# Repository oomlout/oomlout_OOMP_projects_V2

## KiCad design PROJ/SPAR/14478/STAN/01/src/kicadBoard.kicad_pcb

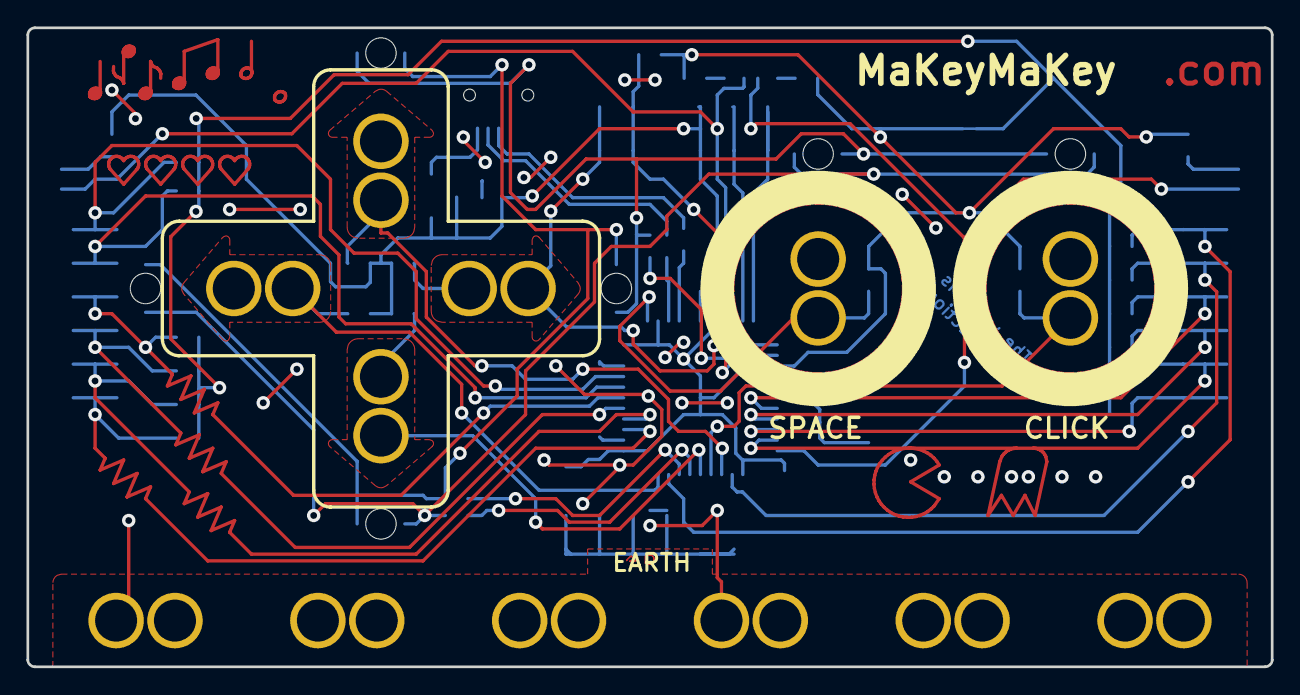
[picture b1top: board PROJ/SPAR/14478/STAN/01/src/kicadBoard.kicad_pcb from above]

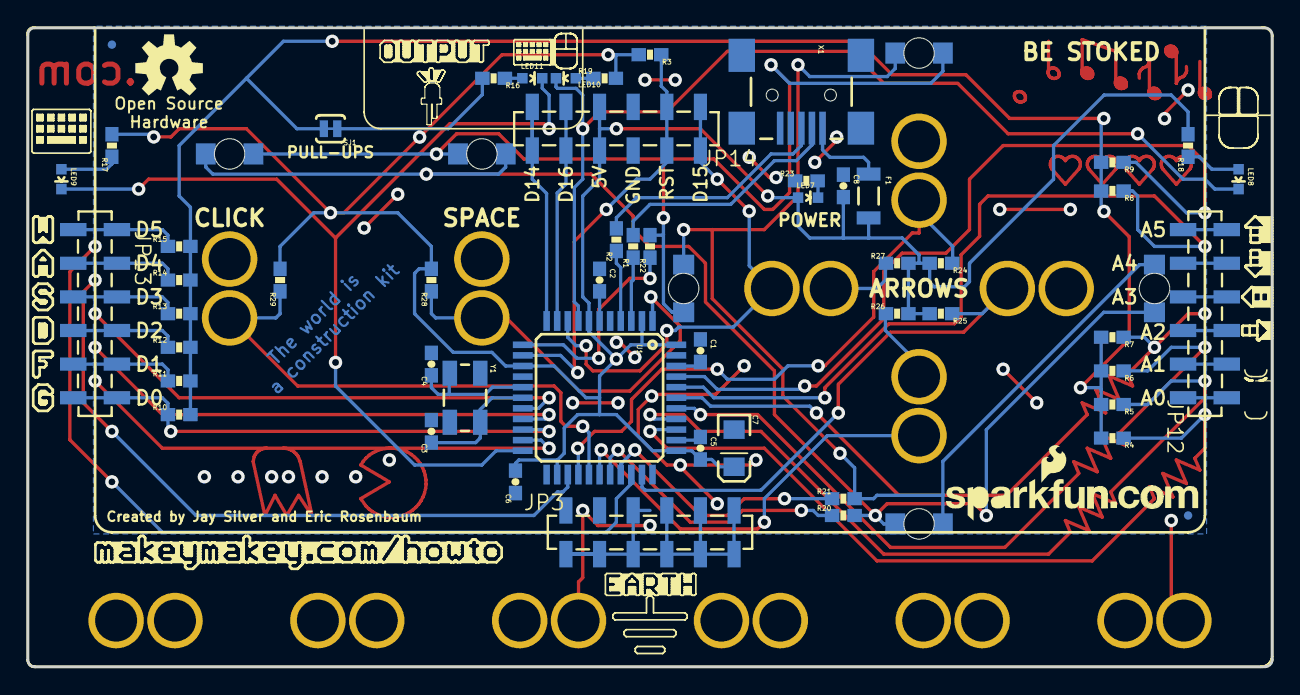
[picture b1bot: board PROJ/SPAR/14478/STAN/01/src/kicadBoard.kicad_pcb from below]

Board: 2 copper layers, 94.0 x 48.3 mm, 73 parts (63 on the bottom side), 46 nets.

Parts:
C1, C5, C8: 0.1uF; 0603-CAP
C2, C6: 1uF; 0603-CAP
C3, C4: 22pF; 0603-CAP
C7: 10uF; EIA3216
CLICK0: 1X01_ALLIGATOR_3MM
DOWN0: 1X01_ALLIGATOR_3MM
F1: 500mA; PTC-1206-WIDE
JP1, JP2: FIDUCIALUFIDUCIAL; MICRO-FIDUCIAL
JP3, JP12, JP13, JP14: 1X06_SMD_STRAIGHT_COMBO
JP5, JP6, JP7, JP8, JP10, JP11: 1X01_ALLIGATOR_3MM
JP9: LOGO-SFENEW; SFE-NEW-WEBLOGO
LED1, LED2, LED3, LED4, LED5, LED6: GREEN; LED-1206-BOTTOM
LED7, LED10, LED11: RED; LED-0603
LED8, LED9: GREEN; LED-0603
LEFT0: 1X01_ALLIGATOR_3MM
R1, R2: 22; 0603-RES
R3: 10K; 0603-RES
R4, R5, R6, R7, R8, R9, R10, R11, R12, R13, R14, R15, R24, R25, R26, R27, R28, R29: 22M; 0603-RES
R16, R19, R23: 1k; 0603-RES
R17, R18, R20, R21, R22: 330; 0603-RES
RIGHT0: 1X01_ALLIGATOR_3MM
SJ1: Pull-ups; SJ_2S-TRACE
SPACE0: 1X01_ALLIGATOR_3MM
U1: ATMEGA32U4TQFP; TQFP44
U$1: OSHW-LOGOM; OSHW-LOGO-M
UP0: 1X01_ALLIGATOR_3MM
X1: USBSMD; USB-MINIB
Y1: 16MHz; CRYSTAL-SMD-5X3

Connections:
A0: JP12.1, JP12.1-2, R4.1, U1.36
A1: JP12.2, JP12.2-2, R5.1, U1.37
A2: JP12.3, JP12.3-2, R6.1, U1.38
A3: JP12.4, JP12.4-2, R7.1, U1.39
A4: JP12.5, JP12.5-2, R8.1, U1.40
A5: JP12.6, JP12.6-2, R9.1, U1.41
AREF: C1.2, U1.42
D0: JP13.6, JP13.6-2, R10.1, U1.20
D1: JP13.5, JP13.5-2, R11.1, U1.21
D2: JP13.4, JP13.4-2, R12.1, U1.19
D3: JP13.3, JP13.3-2, R13.1, U1.18
D4: JP13.2, JP13.2-2, R14.1, U1.25
D5: JP13.1, JP13.1-2, R15.1, U1.31
D6: CLICK0.1@0, CLICK0.1@2, R29.1, U1.27
D7: R28.1, SPACE0.1@0, SPACE0.1@2, U1.1
D8: DOWN0.1@0, DOWN0.1@2, R26.1, U1.28
D9: R20.1, U1.29
D10: R21.1, U1.30
D11: R22.1, U1.12
D12: R24.1, U1.26, UP0.1@0, UP0.1@2
D13: LEFT0.1@0, LEFT0.1@2, R25.1, U1.32
D14: JP14.6, JP14.6-2, U1.11
D15: JP14.1, JP14.1-2, R27.1, RIGHT0.1@0, RIGHT0.1@2, U1.9
D16: JP14.5, JP14.5-2, U1.10
D17: LED8.C, LED10.C, U1.8
D+: R2.1, U1.4
D-: R1.1, U1.3
GND: C1.1, C2.1, C3.2, C4.2, C5.1, C6.1, C7.C, C8.1, JP3.1, JP3.1-2, JP3.2, JP3.2-2, JP3.3, JP3.3-2, JP3.4, JP3.4-2, JP3.5, JP3.5-2, JP3.6, JP3.6-2, JP5.1@0, JP5.1@2, JP6.1@0, JP6.1@2, JP7.1@0, JP7.1@2, JP8.1@0, JP8.1@2, JP10.1@0, JP10.1@2, JP11.1@0, JP11.1@2, JP14.3, JP14.3-2, R23.1, U1.5, U1.15, U1.23, U1.33, U1.35, U1.43, X1.GND
unnamed: C4.1, U1.16, Y1.1
unnamed: C3.1, U1.17, Y1.3
unnamed: LED8.A, R18.1
unnamed: C2.2, U1.6
unnamed: F1.1, X1.VBUS
unnamed: R1.2, X1.D-
unnamed: LED7.C, R23.2
unnamed: R2.2, X1.D+
unnamed: LED11.A, R16.1
unnamed: LED10.A, R19.1
unnamed: LED9.A, R17.1
unnamed: LED1.C, LED2.A, LED5.A, LED6.C, R21.2
unnamed: LED1.A, LED2.C, LED3.A, LED4.C, R20.2
unnamed: LED3.C, LED4.A, LED5.C, LED6.A, R22.2
PD5: LED9.C, LED11.C, U1.22
PULL-UP: R4.2, R5.2, R6.2, R7.2, R8.2, R9.2, R10.2, R11.2, R12.2, R13.2, R14.2, R15.2, SJ1.2
RESET: JP14.2, JP14.2-2, R3.1, U1.13
VCC: C5.2, C6.2, C7.A, C8.2, F1.2, JP14.4, JP14.4-2, LED7.A, R3.2, R16.2, R17.2, R18.2, R19.2, R24.2, R25.2, R26.2, R27.2, R28.2, R29.2, SJ1.1, U1.2, U1.7, U1.14, U1.24, U1.34, U1.44

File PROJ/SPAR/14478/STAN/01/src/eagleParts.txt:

Partlist

Exported from boardEagle.brd at 20/08/2022 00:19

EAGLE Version 9.6.2 Copyright (c) 1988-2020 Autodesk, Inc.

Assembly variant: 

Part     Value             Package                 Library             Position (inch)       Orientation

C1       0.1uF             0603-CAP                SparkFun            (1.7 0.94)            MR270
C2       1uF               0603-CAP                SparkFun            (2 1.15)              MR270
C3       22pF              0603-CAP                SparkFun            (2.5 0.7)             MR90
C4       22pF              0603-CAP                SparkFun            (2.5 0.9)             MR90
C5       0.1uF             0603-CAP                SparkFun            (1.7 0.65)            MR270
C6       1uF               0603-CAP                SparkFun            (2.25 0.55)           MR90
C7       10uF              EIA3216                 SparkFun            (1.6 0.65)            MR270
C8       0.1uF             0603-CAP                SparkFun            (1.275 1.43)          MR270
CLICK                      1X01_ALLIGATOR_3MM      SparkFun-Connectors (3.1 1.125)           MR180
DOWN                       1X01_ALLIGATOR_3MM      SparkFun-Connectors (1.05 0.775)          R0
F1       500mA             PTC-1206-WIDE           SparkFun-PowerIC    (1.2 1.4)             MR270
JP1      FIDUCIALUFIDUCIAL MICRO-FIDUCIAL          SparkFun            (3.45 1.85)           MR0
JP2      FIDUCIALUFIDUCIAL MICRO-FIDUCIAL          SparkFun            (0.25 0.45)           MR0
JP3                        1X06_SMD_STRAIGHT_COMBO SparkFun-Connectors (2.1 0.4)             MR0
JP5                        1X01_ALLIGATOR_3MM      SparkFun-Connectors (3.35 0.1375)         R90
JP6                        1X01_ALLIGATOR_3MM      SparkFun-Connectors (2.75 0.1375)         R90
JP7                        1X01_ALLIGATOR_3MM      SparkFun-Connectors (2.15 0.1375)         R90
JP8                        1X01_ALLIGATOR_3MM      SparkFun-Connectors (1.55 0.1375)         R90
JP10                       1X01_ALLIGATOR_3MM      SparkFun-Connectors (0.95 0.1375)         R90
JP11                       1X01_ALLIGATOR_3MM      SparkFun-Connectors (0.35 0.1375)         R90
JP12                       1X06_SMD_STRAIGHT_COMBO SparkFun-Connectors (0.2 0.8)             MR90
JP13                       1X06_SMD_STRAIGHT_COMBO SparkFun-Connectors (3.5 1.3)             MR270
JP14                       1X06_SMD_STRAIGHT_COMBO SparkFun-Connectors (1.7 1.6)             MR180
LED1     GREEN             LED-1206-BOTTOM         SparkFun-LED        (1.05 0.425)          MR0
LED2     GREEN             LED-1206-BOTTOM         SparkFun-LED        (0.35 1.125)          MR270
LED3     GREEN             LED-1206-BOTTOM         SparkFun-LED        (3.1 1.525)           MR0
LED4     GREEN             LED-1206-BOTTOM         SparkFun-LED        (2.35 1.525)          MR0
LED5     GREEN             LED-1206-BOTTOM         SparkFun-LED        (1.05 1.825)          MR0
LED6     GREEN             LED-1206-BOTTOM         SparkFun-LED        (1.75 1.125)          MR90
LED7     RED               LED-0603                SparkFun            (1.38 1.395)          MR270
LED8     GREEN             LED-0603                SparkFun-LED        (0.1 1.45)            MR180
LED9     GREEN             LED-0603                SparkFun-LED        (3.6 1.45)            MR180
LED10    RED               LED-0603                SparkFun-LED        (2.1 1.75)            MR90
LED11    RED               LED-0603                SparkFun-LED        (2.2 1.75)            MR270
LEFT                       1X01_ALLIGATOR_3MM      SparkFun-Connectors (0.7 1.125)           R270
R1       22                0603-RES                SparkFun            (1.9 1.25)            MR90
R2       22                0603-RES                SparkFun            (1.95 1.27)           MR90
R3       10K               0603-RES                SparkFun            (1.85 1.82)           MR180
R4       22M               0603-RES                SparkFun            (0.475 0.68)          MR180
R5       22M               0603-RES                SparkFun            (0.475 0.78)          MR180
R6       22M               0603-RES                SparkFun            (0.475 0.88)          MR180
R7       22M               0603-RES                SparkFun            (0.475 0.98)          MR180
R8       22M               0603-RES                SparkFun            (0.475 1.415)         MR180
R9       22M               0603-RES                SparkFun            (0.475 1.5)           MR180
R10      22M               0603-RES                SparkFun            (3.25 0.75)           MR0
R11      22M               0603-RES                SparkFun            (3.25 0.85)           MR0
R12      22M               0603-RES                SparkFun            (3.25 0.95)           MR0
R13      22M               0603-RES                SparkFun            (3.25 1.05)           MR0
R14      22M               0603-RES                SparkFun            (3.25 1.15)           MR0
R15      22M               0603-RES                SparkFun            (3.25 1.25)           MR0
R16      1k                0603-RES                SparkFun-Passives   (2.315 1.75)          MR180
R17      330               0603-RES                SparkFun-Passives   (3.45 1.55)           MR90
R18      330               0603-RES                SparkFun-Passives   (0.25 1.55)           MR90
R19      1k                0603-RES                SparkFun-Passives   (1.985 1.75)          MR0
R20      330               0603-RES                SparkFun-Passives   (1.275 0.45)          MR0
R21      330               0603-RES                SparkFun-Passives   (1.275 0.5)           MR0
R22      330               0603-RES                SparkFun-Passives   (1.85 1.25)           MR90
R23      1k                0603-RES                SparkFun            (1.385 1.445)         MR0
R24      22M               0603-RES                SparkFun            (0.985 1.2)           MR180
R25      22M               0603-RES                SparkFun            (0.985 1.05)          MR180
R26      22M               0603-RES                SparkFun            (1.115 1.05)          MR0
R27      22M               0603-RES                SparkFun            (1.115 1.2)           MR0
R28      22M               0603-RES                SparkFun            (2.5 1.15)            MR90
R29      22M               0603-RES                SparkFun            (2.95 1.15)           MR90
RIGHT                      1X01_ALLIGATOR_3MM      SparkFun-Connectors (1.4 1.125)           R270
SJ1      Pull-ups          SJ_2S-TRACE             SparkFun            (2.8 1.6)             MR180
SPACE                      1X01_ALLIGATOR_3MM      SparkFun-Connectors (2.35 1.125)          MR180
U1       ATMEGA32U4TQFP    TQFP44                  SparkFun-DigitalIC  (2 0.8)               MR270
UP                         1X01_ALLIGATOR_3MM      SparkFun-Connectors (1.05 1.475)          R0
X1       USBSMD            USB-MINIB               SparkFun            (1.4 1.7)             MR270
Y1       16MHz             CRYSTAL-SMD-5X3         SparkFun            (2.4 0.8)             MR270

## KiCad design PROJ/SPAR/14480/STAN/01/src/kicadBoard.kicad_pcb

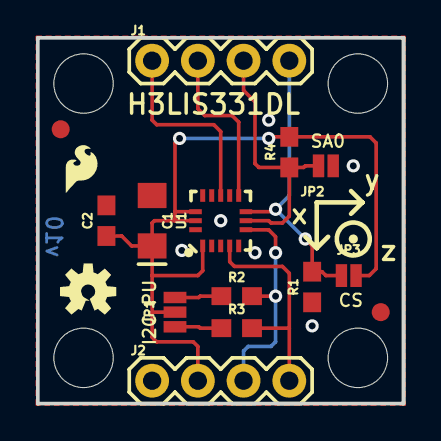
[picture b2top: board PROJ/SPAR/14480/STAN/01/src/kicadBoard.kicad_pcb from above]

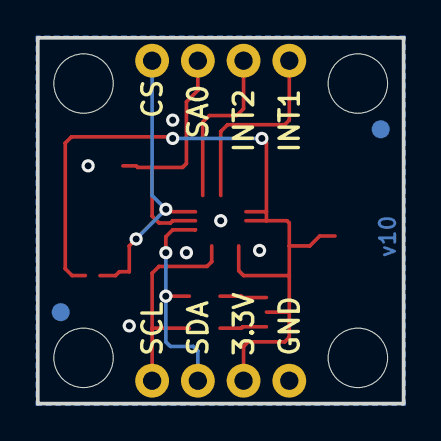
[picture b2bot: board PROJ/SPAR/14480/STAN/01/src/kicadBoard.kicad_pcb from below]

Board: 4 copper layers, 20.3 x 20.3 mm, 23 parts (2 on the bottom side), 10 nets.

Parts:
C1: 10uF; EIA3216
C2: 0.1uF; 0603
FRAME1: FRAME-LETTER; CREATIVE_COMMONS
J1, J2: 1X04
JP1: JUMPER-SMT_3_2-NC_PASTE_NO-SILK; SMT-JUMPER_3_2-NC_PASTE_NO-SILK
JP2: JUMPER-SMT_2_NO_NO-SILK; SMT-JUMPER_2_NO_NO-SILK
JP3: JUMPER-SMT_2_NC_PASTE_NO-SILK; SMT-JUMPER_2_NC_PASTE_NO-SILK
JP4, JP5, JP6, JP7: FIDUCIAL1X2; FIDUCIAL-1X2
JP8, JP9, JP10, JP11: STAND-OFF
LOGO1: SFE_LOGO_FLAME.1_INCH; SFE_LOGO_FLAME_.1
LOGO2: OSHW-LOGOS; OSHW-LOGO-S
R1, R4: 10k; 0603
R2, R3: 4.7k; 0603
U1: H3LIS331DL; LGA-16-3X3

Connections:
3.3V: C1.+, C2.1, J2.2, JP1.2, JP3.2, R4.2, U1.1, U1.14, U1.15
CS: J1.4, JP3.1, R1.2, U1.8
GND: C1.-, C2.2, J2.1, JP2.1, R1.1, U1.5, U1.10, U1.12, U1.13, U1.16
INT1: J1.1, U1.11
INT2: J1.2, U1.9
unnamed: JP1.1, R3.1
unnamed: JP1.3, R2.1
SA0: J1.3, JP2.2, R4.1, U1.7
SCL: J2.4, R3.2, U1.4
SDA: J2.3, R2.2, U1.6

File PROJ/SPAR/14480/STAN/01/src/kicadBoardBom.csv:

"Id";"Designator";"Package";"Quantity";"Designation";"Supplier and ref";
1;"JP11,JP9,JP8,JP10";"STAND-OFF";4;"STAND-OFF";;;
2;"R4,R1";"0603";2;"10k";;;
3;"C2";"0603";1;"0.1uF";;;
4;"C1";"EIA3216";1;"10uF";;;
5;"JP1";"SMT-JUMPER_3_2-NC_PASTE_NO-SILK";1;"JUMPER-SMT_3_2-NC_PASTE_NO-SILK";;;
6;"JP3";"SMT-JUMPER_2_NC_PASTE_NO-SILK";1;"JUMPER-SMT_2_NC_PASTE_NO-SILK";;;
7;"J1,J2";"1X04";2;"";;;
8;"JP4,JP6,JP7,JP5";"FIDUCIAL-1X2";4;"FIDUCIAL1X2";;;
9;"LOGO1";"SFE_LOGO_FLAME_.1";1;"SFE_LOGO_FLAME.1_INCH";;;
10;"R3,R2";"0603";2;"4.7k";;;
11;"FRAME1";"CREATIVE_COMMONS";1;"FRAME-LETTER";;;
12;"U1";"LGA-16-3X3";1;"H3LIS331DL";;;
13;"LOGO2";"OSHW-LOGO-S";1;"OSHW-LOGOS";;;
14;"JP2";"SMT-JUMPER_2_NO_NO-SILK";1;"JUMPER-SMT_2_NO_NO-SILK";;;

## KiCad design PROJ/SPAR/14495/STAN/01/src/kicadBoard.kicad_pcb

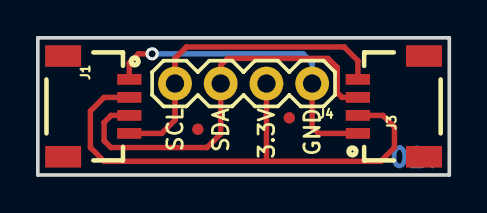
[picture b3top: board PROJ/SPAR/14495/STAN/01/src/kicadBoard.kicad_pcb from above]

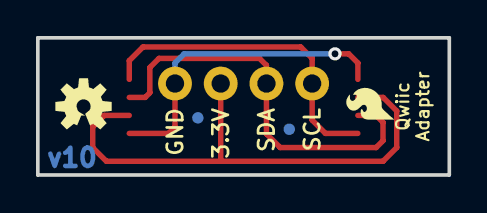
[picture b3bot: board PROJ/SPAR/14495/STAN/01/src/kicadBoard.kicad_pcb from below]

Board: 2 copper layers, 22.9 x 7.6 mm, 11 parts (4 on the bottom side), 4 nets.

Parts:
FD1, FD2, FD3, FD4: FIDUCIALUFIDUCIAL; FIDUCIAL-MICRO
FRAME1: FRAME-LETTER; CREATIVE_COMMONS
J1, J3: 1X04_1MM_RA
J4: PTH; 1X04
LOGO1: REVISION
LOGO4: OSHW-LOGOS; OSHW-LOGO-S
U$1: SFE_LOGO_FLAME.1_INCH; SFE_LOGO_FLAME_.1

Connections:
3.3V: J1.2, J3.2, J4.2
GND: J1.1, J3.1, J4.1
SCL: J1.4, J3.4, J4.4
SDA: J1.3, J3.3, J4.3

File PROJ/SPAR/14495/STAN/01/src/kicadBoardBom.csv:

"Id";"Designator";"Package";"Quantity";"Designation";"Supplier and ref";
1;"FD3,FD1,FD4,FD2";"FIDUCIAL-MICRO";4;"FIDUCIALUFIDUCIAL";;;
2;"J4";"1X04";1;"PTH";;;
3;"J1,J3";"1X04_1MM_RA";2;"";;;
4;"FRAME1";"CREATIVE_COMMONS";1;"FRAME-LETTER";;;
5;"LOGO1";"REVISION";1;"REVISION";;;
6;"U$1";"SFE_LOGO_FLAME_.1";1;"SFE_LOGO_FLAME.1_INCH";;;
7;"LOGO4";"OSHW-LOGO-S";1;"OSHW-LOGOS";;;

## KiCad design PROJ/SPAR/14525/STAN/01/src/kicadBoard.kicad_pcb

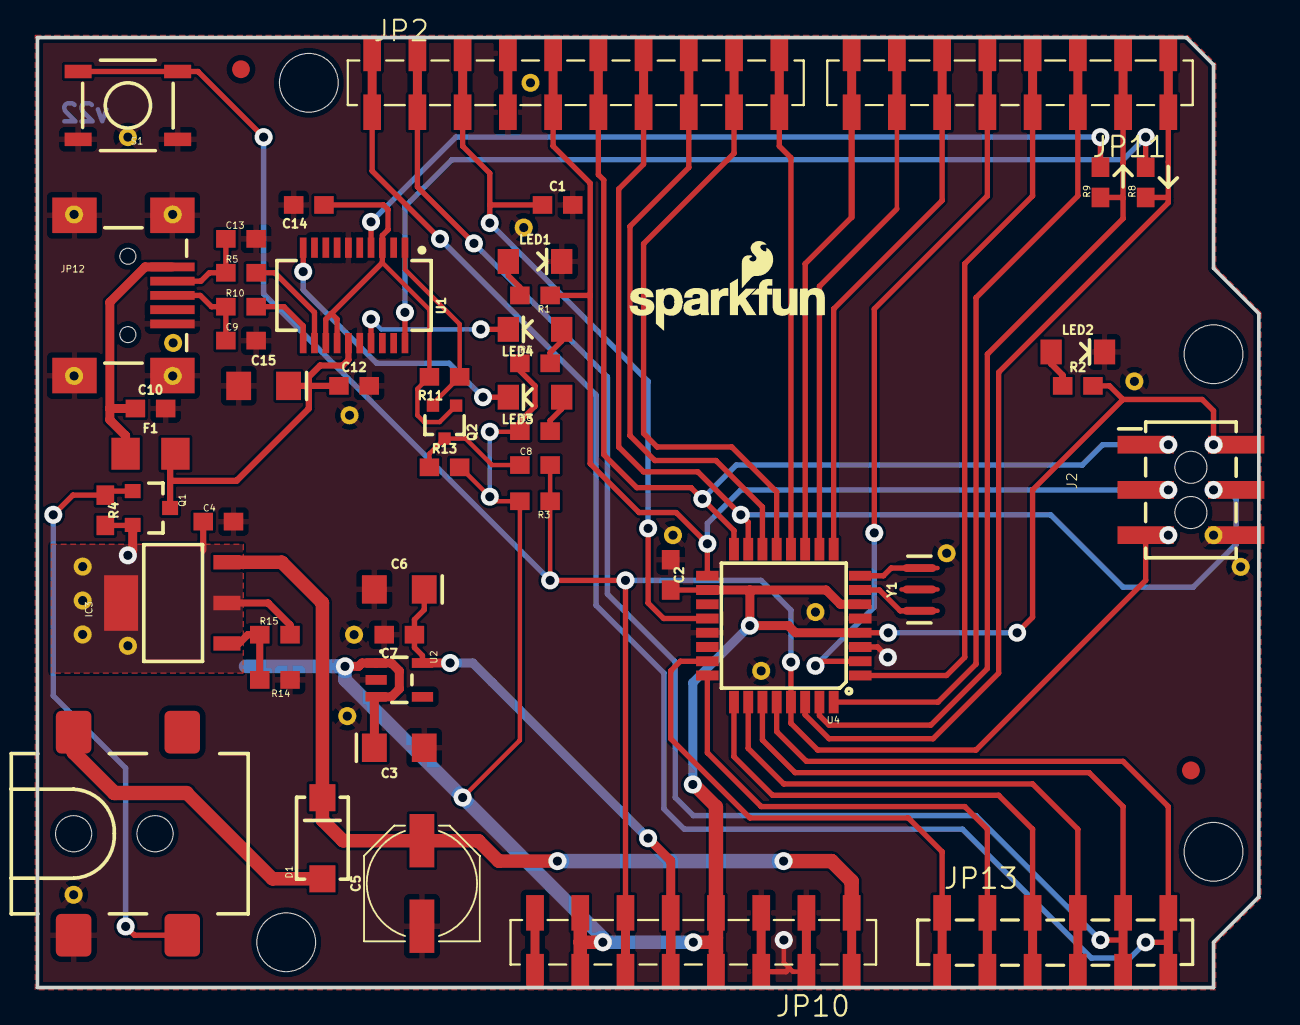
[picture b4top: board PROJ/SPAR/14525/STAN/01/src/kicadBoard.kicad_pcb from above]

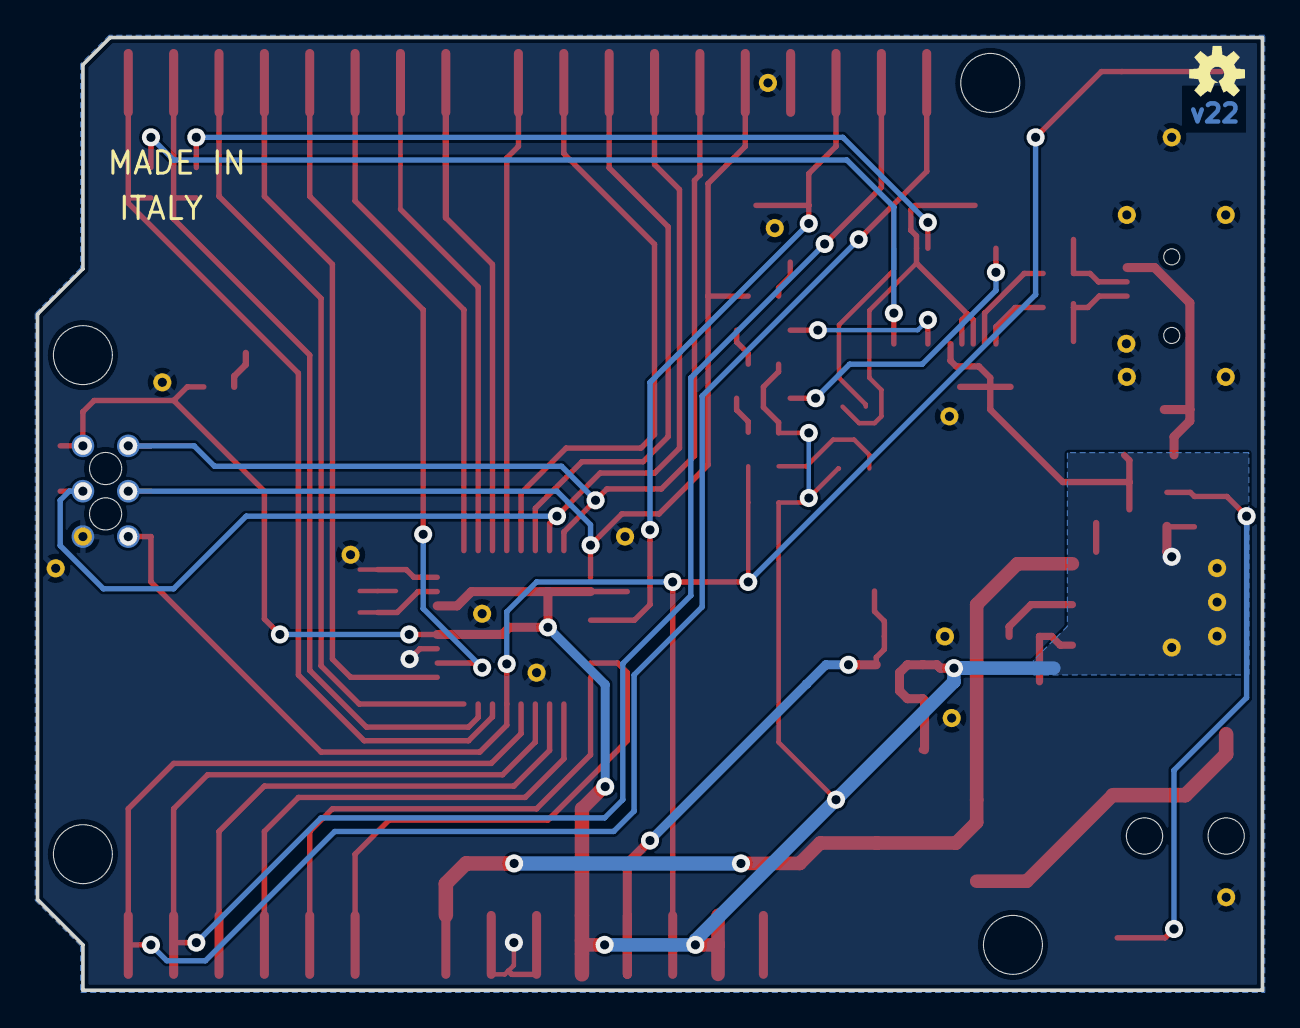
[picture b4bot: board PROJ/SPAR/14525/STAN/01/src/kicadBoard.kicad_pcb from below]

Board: 2 copper layers, 68.6 x 53.3 mm, 88 parts (7 on the bottom side), 48 nets.

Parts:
C1, C2, C4, C8, C10, C12, C14: 0.1uF; 0603
C3, C6, C15: 10uF; EIA3216
C5: 47uF; PANASONIC_D
C7: 1.0uF; 0603
C9, C13: 47pF; 0603
D1: MBRA140; SMA-DIODE
F1: 6V/0.5A; 1206
FRAME2: FRAME-LETTER; CREATIVE_COMMONS
IC3: LM1117; SOT223-ALT1
J2: ICSP; 2X3_SMT_POSTS
J3: POWER_JACKSUPER_BOMB_DIGITY; POWER_JACK_SMD_OVERPASTE_SUPER_BOMB_DIGITY
JP1: SFE_LOGO_NAME.1_INCH; SFE_LOGO_NAME_.1
JP2: M10SMD_COMBO; 1X10_SMD_COMBINED
JP3, JP4, JP5, JP6: STAND-OFF
JP7: SFE_LOGO_FLAME.1_INCH; SFE_LOGO_FLAME_.1
JP8, JP9: FIDUCIAL1X2; FIDUCIAL-1X2
JP10: JP10; 1X08_SMD_COMBINED
JP11: IOL; 1X08_SMD_COMBINED
JP12: USB-MINIB-5PIN; USB-MINIB
JP13: AD; 1X06_SMD_STRAIGHT_COMBO
LED1: Blue; LED-1206
LED2: Green; LED-1206
LED3: Red; LED-1206
LED4: Yellow; LED-1206
Q1: 1A/60V/500mΩ; SOT23-3
Q2: 2N7002PW; SOT323
R1, R6, R7, R8, R9: 1k; 0603
R2: 4.7k; 0603
R3, R4, R11, R13: 10k; 0603
R5, R10: 27; 0603
R14: 715; 0603
R15: 240; 0603
S1: RESET; TACTILE-SWITCH-SMD
TP1, TP2, TP3, TP4, TP5, TP6: TP-3x5; PAD.03X.05
U1: FT231XS; SSOP20_L
U2: MIC5205; SOT23-5
U4: ATMEGA328P_TQFP; TQFP32-08
U$16: OSHW-LOGOS; OSHW-LOGO-S
VP_0, VP_1, VP_2, VP_3, VP_4, VP_5, VP_6, VP_7, VP_8, VP_9, VP_10, VP_11, VP_12, VP_13, VP_14, VP_15, VP_16, VP_17, VP_18, VP_19, VP_20, VP_21, VP_22: VPDEV0; VPAC0
Y1: 16MHz; RESONATOR-SMD-3.2X1.3

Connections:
3.3V: C6.+, C7.1, JP10.5A, JP10.5B, U2.5
3.3V_F: C14.1, Q2.1, R11.2, U1.3, U1.13, U1.14
5V: C2.2, C3.+, C4.1, IC3.2, IC3.4, J2.2, JP10.4A, JP10.4B, JP10.7A, JP10.7B, Q1.2, R2.2, R3.2, R4.2, R6.1, R7.1, R13.2, R15.2, TP1.P$1, U2.1, U2.3, U4.4, U4.6, U4.18, VP_0.VP, VP_1.VP, VP_2.VP, VP_3.VP
AD0: JP13.1A, JP13.1B, U4.23
AD1: JP13.2A, JP13.2B, U4.24
AD2: JP13.3A, JP13.3B, U4.25
AD3: JP13.4A, JP13.4B, U4.26
AD4/SDA: JP2.2A, JP2.2B, JP13.5A, JP13.5B, U4.27
AD5/SCL: JP2.1A, JP2.1B, JP13.6A, JP13.6B, U4.28
AREF: C1.1, JP2.3A, JP2.3B, U4.20
D+: C9.1, JP12.D+, R10.1
D-: C13.1, JP12.D-, R5.1
DTR: C8.1, Q2.3, R13.1
FTDI_DTR: Q2.2, R11.1, U1.1
GND: C1.2, C2.1, C3.-, C4.2, C5.-, C6.-, C7.2, C9.2, C10.2, C12.2, C13.2, C14.2, C15.-, J2.6, J3.GND, JP2.4A, JP2.4B, JP10.2A, JP10.2B, JP10.3A, JP10.3B, JP12.GND, JP12.MTN1, JP12.MTN2, JP12.MTN3, JP12.MTN4, LED1.C, LED2.C, R14.1, S1.1, S1.2, TP3.P$1, U1.6, U1.16, U2.2, U4.3, U4.5, U4.21, VP_4.VP, VP_5.VP, VP_6.VP, VP_7.VP, VP_8.VP, VP_9.VP, VP_10.VP, VP_11.VP, VP_12.VP, VP_13.VP, VP_14.VP, VP_15.VP, VP_16.VP, VP_17.VP, VP_18.VP, VP_19.VP, VP_20.VP, VP_21.VP, VP_22.VP, Y1.2
INSERT: J3.P$4, Q1.1, R4.1
IO2: JP11.3A, JP11.3B, U4.32
IO3: JP11.4A, JP11.4B, U4.1
IO4: JP11.5A, JP11.5B, U4.2
IO5: JP11.6A, JP11.6B, U4.9
IO6: JP11.7A, JP11.7B, U4.10
IO7: JP11.8A, JP11.8B, U4.11
IO8: JP2.10A, JP2.10B, U4.12
IO9: JP2.9A, JP2.9B, U4.13
MISO: J2.1, JP2.6A, JP2.6B, TP4.P$1, U4.16
MOSI: J2.4, JP2.7A, JP2.7B, TP2.P$1, U4.15
unnamed: LED1.A, R1.2
unnamed: LED2.A, R2.1
unnamed: U4.7, Y1.1
unnamed: U4.8, Y1.3
unnamed: R5.2, U1.12
unnamed: R10.2, U1.11
unnamed: LED3.A, R6.2
unnamed: LED4.A, R7.2
unnamed: IC3.1, R14.2, R15.1
PWRIN: D1.A, J3.VIN0
RESET: C8.2, J2.5, JP10.6A, JP10.6B, R3.1, S1.3, S1.4, TP6.P$1, U4.29
RX-I: JP11.1A, JP11.1B, R8.1, U4.30
RXD: R9.2, U1.4
RXLED: LED4.C, U1.17
SCK: J2.3, JP2.5A, JP2.5B, R1.1, TP5.P$1, U4.17
SS: JP2.8A, JP2.8B, U4.14
TX-O: JP11.2A, JP11.2B, R9.1, U4.31
TXD: R8.2, U1.20
TXLED: LED3.C, U1.10
USBVCC: C12.1, C15.+, F1.2, Q1.3, U1.15
VIN: C5.+, D1.C, IC3.3, JP10.1A, JP10.1B
VUSB: C10.1, F1.1, JP12.VBUS

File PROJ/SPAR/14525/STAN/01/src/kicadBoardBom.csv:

"Id";"Designator";"Package";"Quantity";"Designation";"Supplier and ref";
1;"C4,C12,C2,C14,C1,C8,C10";"0603";7;"0.1uF";;;
2;"S1";"TACTILE-SWITCH-SMD";1;"RESET";;;
3;"VP_14,VP_17,VP_1,VP_6,VP_9,VP_11,VP_16,VP_12,VP_13,VP_22,VP_20,VP_10,VP_18,VP_15,VP_2,VP_4,VP_0,VP_8,VP_3,VP_5,VP_7,VP_21,VP_19";"VPAC0";23;"VPDEV0";;;
4;"C13,C9";"0603";2;"47pF";;;
5;"R7,R9,R8,R6,R1";"0603";5;"1k";;;
6;"J3";"POWER_JACK_SMD_OVERPASTE_SUPER_BOMB_DIGITY";1;"POWER_JACKSUPER_BOMB_DIGITY";;;
7;"JP13";"1X06_SMD_STRAIGHT_COMBO";1;"AD";;;
8;"JP6,JP4,JP5,JP3";"STAND-OFF";4;"STAND-OFF";;;
9;"Y1";"RESONATOR-SMD-3.2X1.3";1;"16MHz";;;
10;"JP2";"1X10_SMD_COMBINED";1;"M10SMD_COMBO";;;
11;"Q1";"SOT23-3";1;"1A/60V/500mΩ";;;
12;"C5";"PANASONIC_D";1;"47uF";;;
13;"U1";"SSOP20_L";1;"FT231XS";;;
14;"U2";"SOT23-5";1;"MIC5205";;;
15;"C6,C15,C3";"EIA3216";3;"10uF";;;
16;"LED1";"LED-1206";1;"Blue";;;
17;"IC3";"SOT223-ALT1";1;"LM1117";;;
18;"FRAME2";"CREATIVE_COMMONS";1;"FRAME-LETTER";;;
19;"R4,R3,R13,R11";"0603";4;"10k";;;
20;"F1";"1206";1;"6V/0.5A";;;
21;"LED3";"LED-1206";1;"Red";;;
22;"R10,R5";"0603";2;"27";;;
23;"Q2";"SOT323";1;"2N7002PW";;;
24;"U4";"TQFP32-08";1;"ATMEGA328P_TQFP";;;
25;"C7";"0603";1;"1.0uF";;;
26;"R15";"0603";1;"240";;;
27;"JP11";"1X08_SMD_COMBINED";1;"IOL";;;
28;"JP12";"USB-MINIB";1;"USB-MINIB-5PIN";;;
29;"J2";"2X3_SMT_POSTS";1;"ICSP";;;
30;"D1";"SMA-DIODE";1;"MBRA140";;;
31;"LED2";"LED-1206";1;"Green";;;
32;"LED4";"LED-1206";1;"Yellow";;;
33;"R2";"0603";1;"4.7k";;;
34;"JP8,JP9";"FIDUCIAL-1X2";2;"FIDUCIAL1X2";;;
35;"JP10";"1X08_SMD_COMBINED";1;"JP10";;;
36;"JP7";"SFE_LOGO_FLAME_.1";1;"SFE_LOGO_FLAME.1_INCH";;;
37;"R14";"0603";1;"715";;;
38;"JP1";"SFE_LOGO_NAME_.1";1;"SFE_LOGO_NAME.1_INCH";;;
39;"TP5,TP3,TP6,TP2,TP1,TP4";"PAD.03X.05";6;"TP-3x5";;;
40;"U$16";"OSHW-LOGO-S";1;"OSHW-LOGOS";;;

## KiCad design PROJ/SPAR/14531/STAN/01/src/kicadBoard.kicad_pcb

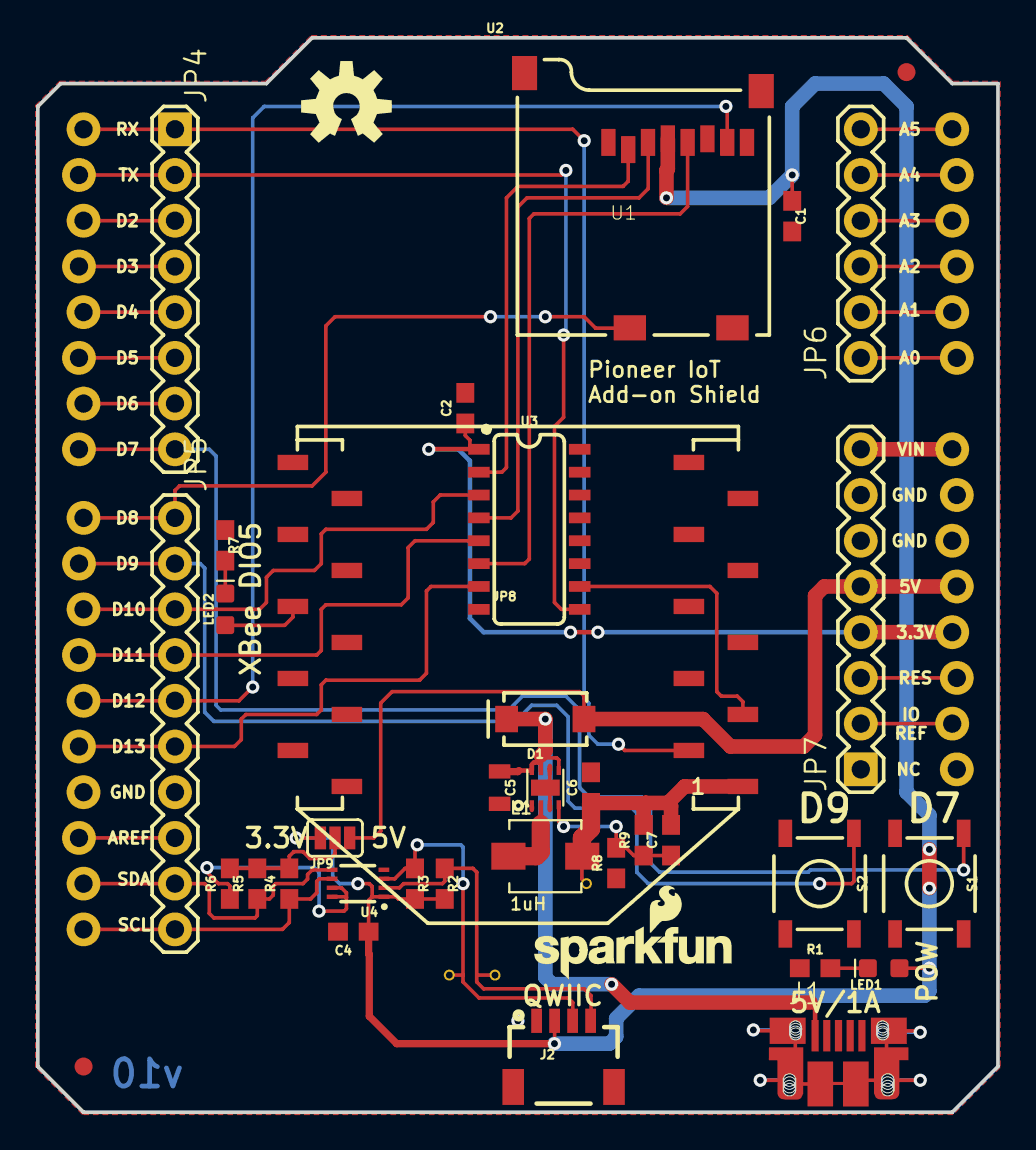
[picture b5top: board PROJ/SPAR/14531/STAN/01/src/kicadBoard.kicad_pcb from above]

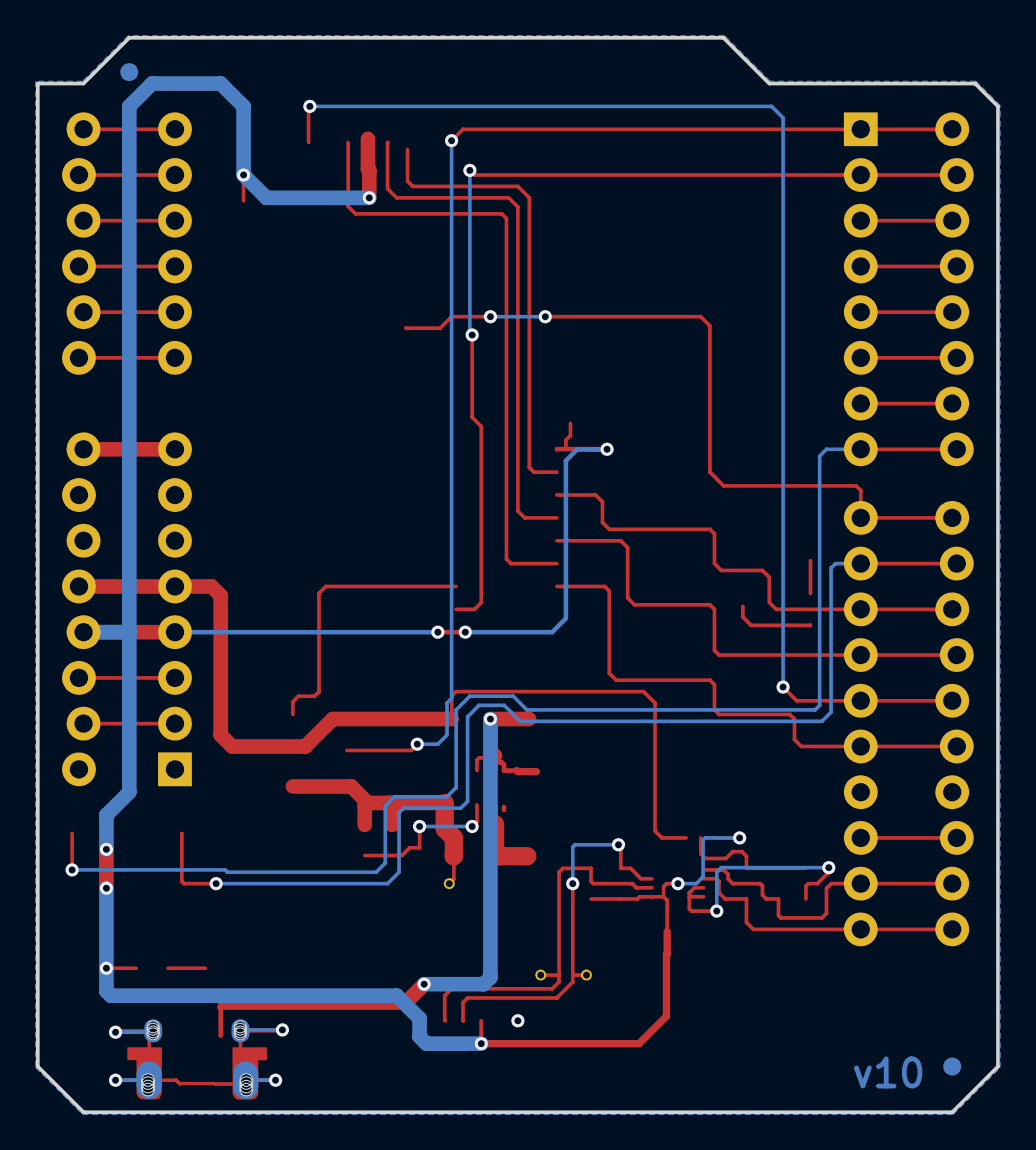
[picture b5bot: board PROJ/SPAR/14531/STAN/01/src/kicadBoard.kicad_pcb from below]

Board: 4 copper layers, 53.3 x 59.7 mm, 45 parts (2 on the bottom side), 45 nets.

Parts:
C1, C2, C4: 0.1uF; 0603
C5: 10uF; 0805
C6: 10uF; 0603
C7: 22pF; 0603
D1: 3A/40V/500mV; SMA-DIODE
FRAME1: FRAME-LETTER; CREATIVE_COMMONS
FRAME2: FRAME-LETTERNO_PACKAGE; DUMMY
J1: AMP FCI 10103594-0001LF; USB-MICROB-PTH
J2: 1X04_1MM_RA
JP1: SFE_LOGO_NAME_FLAME.1_INCH; SFE_LOGO_NAME_FLAME_.1
JP2, JP3, JP10, JP11: FIDUCIAL1X2; FIDUCIAL-1X2
JP4, JP7: 1X08
JP5: M10"; 1X10
JP6: 1X06
JP8: XBEE-SMD
JP9: JUMPER-SMT_3_1-NC_PASTE_SILK; SMT-JUMPER_3_1-NC_PASTE_SILK
L1: 1uH; INDUCTOR-SRP4020
LED1, LED2: RED; LED-0603
LOGO1: OSHW-LOGOM; OSHW-LOGO-M
R1, R7: 1k; 0603
R2, R3, R4, R5: 10k; 0603
R6: 200k; 0603
R8: 180k; 0603
R9: 820k; 0603
S1, S2: TACTILE_SWITCH_SMD_5.2MM
TP1, TP2, TP3: TEST-POINTTP_15TH_THRU; TP_15TH
U1: USD-SOCKETNEW; MICRO-SD-SOCKET-PP
U2: ARDUINO_UNO_R3_SHIELDUNO_R3_SHIELD_NOLABELS_LOCK; UNO_R3_SHIELD_NOLABELS_LOCK
U3: 74HC4050; SO16
U4: PCA9306; PCA9306DC
U5: TPS62065; WSON-8-PAD

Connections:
3.3V: C1.1, C2.1, C4.1, J2.2, JP7.4, JP9.3, LED1.A, R2.2, R3.2, U1.4, U2.3.3V, U3.1, U4.1
5V: D1.A, JP7.5, JP9.1, U2.5V
A0: JP6.1, U2.A0
A1: JP6.2, U2.A1
A2: JP6.3, U2.A2
A3: JP6.4, U2.A3
A4: JP6.5, U2.A4
A5: JP6.6, U2.A5
AREF: JP5.8, U2.AREF
D2: JP4.3, U2.D2
D3: JP4.4, U2.D3
D4: JP4.5, U2.D4
D5: JP4.6, U2.D5
D6: JP4.7, U2.D6
D7: JP4.8, S1.1, U2.D7
D9: JP5.2, S2.1, U2.D9
GND: C1.2, C2.2, C4.2, C5.2, C6.2, J1.GND, J2.1, JP5.7, JP7.6, JP7.7, JP8.10, R1.1, R7.1, R8.1, S1.3, S2.3, U1.6, U1.GND1, U1.GND3, U2.GND@0, U2.GND@1, U2.GND@2, U3.8, U4.4, U5.1, U5.3, U5.6, U5.PAD
IOREF: JP7.2, U2.IOREF
MISO: JP5.5, U1.7, U2.D12
MOSI: JP5.4, U2.D11, U3.5
unnamed: LED2.C, R7.2
unnamed: U1.3, U3.4
unnamed: JP8.15, LED2.A
unnamed: U1.5, U3.6
unnamed: LED1.C, R1.2
unnamed: JP9.2, R4.2, R5.2, R6.2
unnamed: R6.1, U4.7, U4.8
unnamed: C5.1, D1.C, J1.VBUS, U5.5, U5.7, U5.8
unnamed: C7.1, R8.2, R9.1, U5.4
unnamed: L1.P$1, U5.2
unnamed: U1.2, U3.2
RES: JP7.3, U2.RES
RX: JP4.1, JP8.2, U2.RX
SCK: JP5.6, U2.D13, U3.7
SCL: JP5.10, R4.1, U2.SCL, U4.6
SCL_2: J2.4, R2.1, TP1.P$1, U4.2
SDA: JP5.9, R5.1, U2.SDA, U4.5
SDA_2: J2.3, R3.1, TP2.P$1, U4.3
SHIELD: J1.P$1, J1.P$2, J1.P$3, J1.P$4, J1.P$6, J1.P$8, J1.P$10, J1.P$12, J1.SHEILD2, J1.SHIELD, J1.SHIELD3, J1.SHIELD4
TX: JP4.2, U2.TX, U3.9
TX_LV: JP8.3, U3.10
VCC: C6.1, C7.2, JP8.1, L1.P$2, R9.2, TP3.P$1
VIN: JP7.8, U2.VIN
~CD: JP5.1, U1.CD2, U2.D8
~CS: JP5.3, U2.D10, U3.3

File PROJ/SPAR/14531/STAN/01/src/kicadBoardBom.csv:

"Id";"Designator";"Package";"Quantity";"Designation";"Supplier and ref";
1;"TP1,TP2,TP3";"TP_15TH";3;"TEST-POINTTP_15TH_THRU";;;
2;"JP7,JP4";"1X08";2;"";;;
3;"C4,C2,C1";"0603";3;"0.1uF";;;
4;"R3,R5,R4,R2";"0603";4;"10k";;;
5;"U1";"MICRO-SD-SOCKET-PP";1;"USD-SOCKETNEW";;;
6;"D1";"SMA-DIODE";1;"3A/40V/500mV";;;
7;"C7";"0603";1;"22pF";;;
8;"JP8";"XBEE-SMD";1;"";;;
9;"JP5";"1X10";1;"M10"";;;
10;"JP9";"SMT-JUMPER_3_1-NC_PASTE_SILK";1;"JUMPER-SMT_3_1-NC_PASTE_SILK";;;
11;"U2";"UNO_R3_SHIELD_NOLABELS_LOCK";1;"ARDUINO_UNO_R3_SHIELDUNO_R3_SHIELD_NOLABELS_LOCK";;;
12;"LOGO1";"OSHW-LOGO-M";1;"OSHW-LOGOM";;;
13;"C5";"0805";1;"10uF";;;
14;"LED2,LED1";"LED-0603";2;"RED";;;
15;"JP2,JP3,JP11,JP10";"FIDUCIAL-1X2";4;"FIDUCIAL1X2";;;
16;"U4";"PCA9306DC";1;"PCA9306";;;
17;"JP6";"1X06";1;"";;;
18;"R9";"0603";1;"820k";;;
19;"U5";"WSON-8-PAD";1;"TPS62065";;;
20;"C6";"0603";1;"10uF";;;
21;"JP1";"SFE_LOGO_NAME_FLAME_.1";1;"SFE_LOGO_NAME_FLAME.1_INCH";;;
22;"FRAME1";"CREATIVE_COMMONS";1;"FRAME-LETTER";;;
23;"U3";"SO16";1;"74HC4050";;;
24;"L1";"INDUCTOR-SRP4020";1;"1uH";;;
25;"J2";"1X04_1MM_RA";1;"";;;
26;"R6";"0603";1;"200k";;;
27;"R7,R1";"0603";2;"1k";;;
28;"S1,S2";"TACTILE_SWITCH_SMD_5.2MM";2;"";;;
29;"J1";"USB-MICROB-PTH";1;"AMP FCI 10103594-0001LF";;;
30;"R8";"0603";1;"180k";;;
31;"FRAME2";"DUMMY";1;"FRAME-LETTERNO_PACKAGE";;;

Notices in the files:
parts and their libraries:
HTTPS://CREATIVECOMMONS.ORG/LICENSES/BY-SA/4.0
RELEASED UNDER THE CREATIVE COMMONS ATTRIBUTION SHARE-ALIKE 4.0 LICENSE
